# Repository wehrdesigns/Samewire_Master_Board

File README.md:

Samewire_Master_Board
=====================

Master Board Eagle files for the Samewire Sense and Control Network.  The master board connects to a computer through a serial interface and provides power and communication to the samewire network.  The samewire network is a two wire network.  One wire is ground and the other is power and communication.

This board is part of the DISC System (Distributed Intelligent Sense and Control).

More information about can be found at www.wehrdesigns.com.

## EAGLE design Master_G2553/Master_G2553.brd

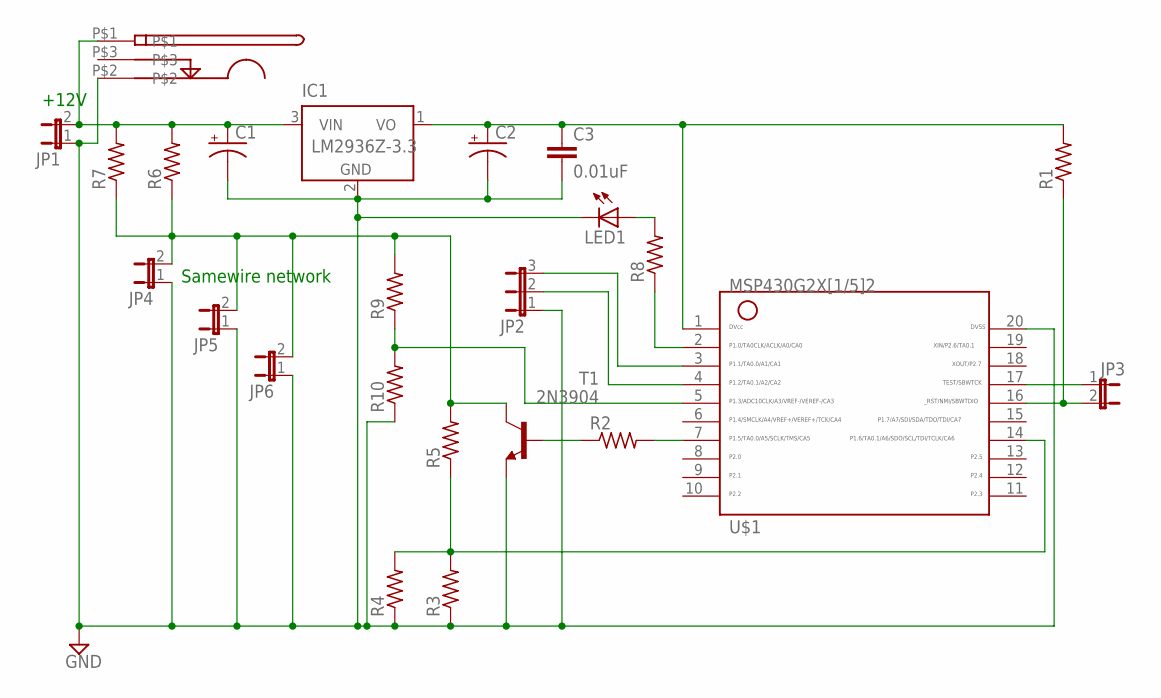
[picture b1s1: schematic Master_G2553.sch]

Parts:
C1, C2: CPOL-USE2.5-6; E2,5-6
C3: 0.01uF; C7.5B3
IC1: LM2936Z-3.3; TO92
JP1, JP3, JP4, JP5, JP6: JP1E; JP1
JP2: JP2E; JP2
LED1: LED3MM
R1, R2, R3, R4, R5, R6, R7, R8, R9, R10: R-US_0204/2V; 0204V
T1: 2N3904; TO92
U$1: G2X[1/5]2---N20; N20
U$2: 2.1MM_5.5MM

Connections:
GND: C1.-, C2.-, C3.2, IC1.2 (GND), JP1.1, JP2.1, JP4.1, JP5.1, JP6.1, LED1.K (C), R3.1, R4.1, R10.1, T1.3 (E), U$1.20, U$2.P$2
unnamed: JP2.2, U$1.4
unnamed: R2.1, T1.2 (B)
unnamed: C1.+, IC1.3 (VIN), JP1.2, R6.2, R7.2, U$2.P$1
unnamed: JP4.2, JP5.2, JP6.2, R5.2, R6.1, R7.1, R9.2, T1.1 (C)
unnamed: R3.2, R4.2, R5.1, U$1.14
unnamed: JP2.3, U$1.3
unnamed: JP3.1, U$1.17
unnamed: R2.2, U$1.7
unnamed: C2.+, C3.1, IC1.1 (VO), R1.2, U$1.1
unnamed: LED1.A, R8.2
unnamed: R9.1, R10.2, U$1.5
unnamed: R8.1, U$1.2
unnamed: JP3.2, R1.1, U$1.16

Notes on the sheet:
+12V
Samewire network

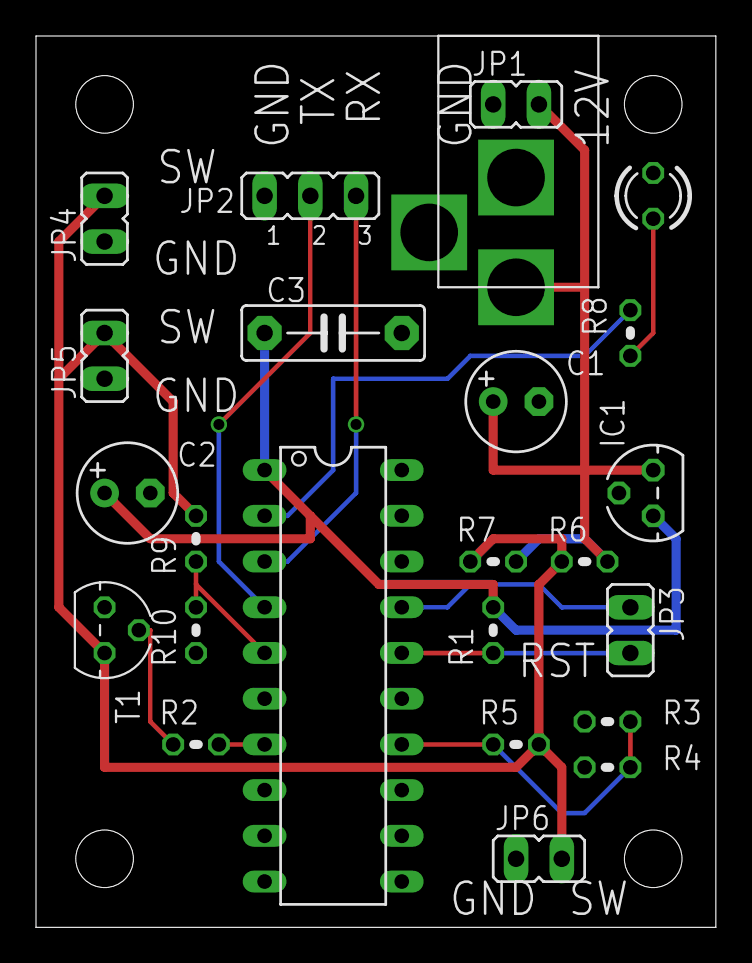
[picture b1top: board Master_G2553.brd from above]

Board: 2 copper layers, 37.8 x 49.5 mm, 24 parts (0 on the bottom side), 14 nets.

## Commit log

2015-01-22 :neckbeard: Added .gitattributes & .gitignore files
2015-01-22 Upload Rev A
